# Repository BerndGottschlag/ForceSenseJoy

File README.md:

# ForceSenseJoy

This joystick measures the force applied by the user and not the deflection as done by conventional joysticks.

## Operating principle

The force is measured using two strain gauges each for the x- and y-axis.
These strain gauges are used in a half-bridge Wheatstone bridge configuration.
The signal from the bridge are amplified by an instrumentation amplifier and then read out using 13-bit analog-digital-converters.
The LUFA library is used to create a USB-joystick device.

## Status

At the moment there are some problems.
The calibration of the Wheatstone bridges is far from perfect.
On one hand this leads to a laborious adjustment process using the trim pots to balance the arms of the bridge and on the other hand the signal sometimes drifts over time.
While the adjustment does not have to be perfect, as the center point (zero) can be set via software on the press of a button,
a bigger imbalance of the bridges will make the amplifier to be unable to amplify the signal to its maximum amplitude.
A possible sollution to this would be the adjustment of the reference voltage.

## How to build
The make script is situated in firmware/src/.  
The project can be build and flashed with
```
make avrdude
```

## License

This project is licensed under the MIT License - see the [LICENSE](LICENSE) file for details

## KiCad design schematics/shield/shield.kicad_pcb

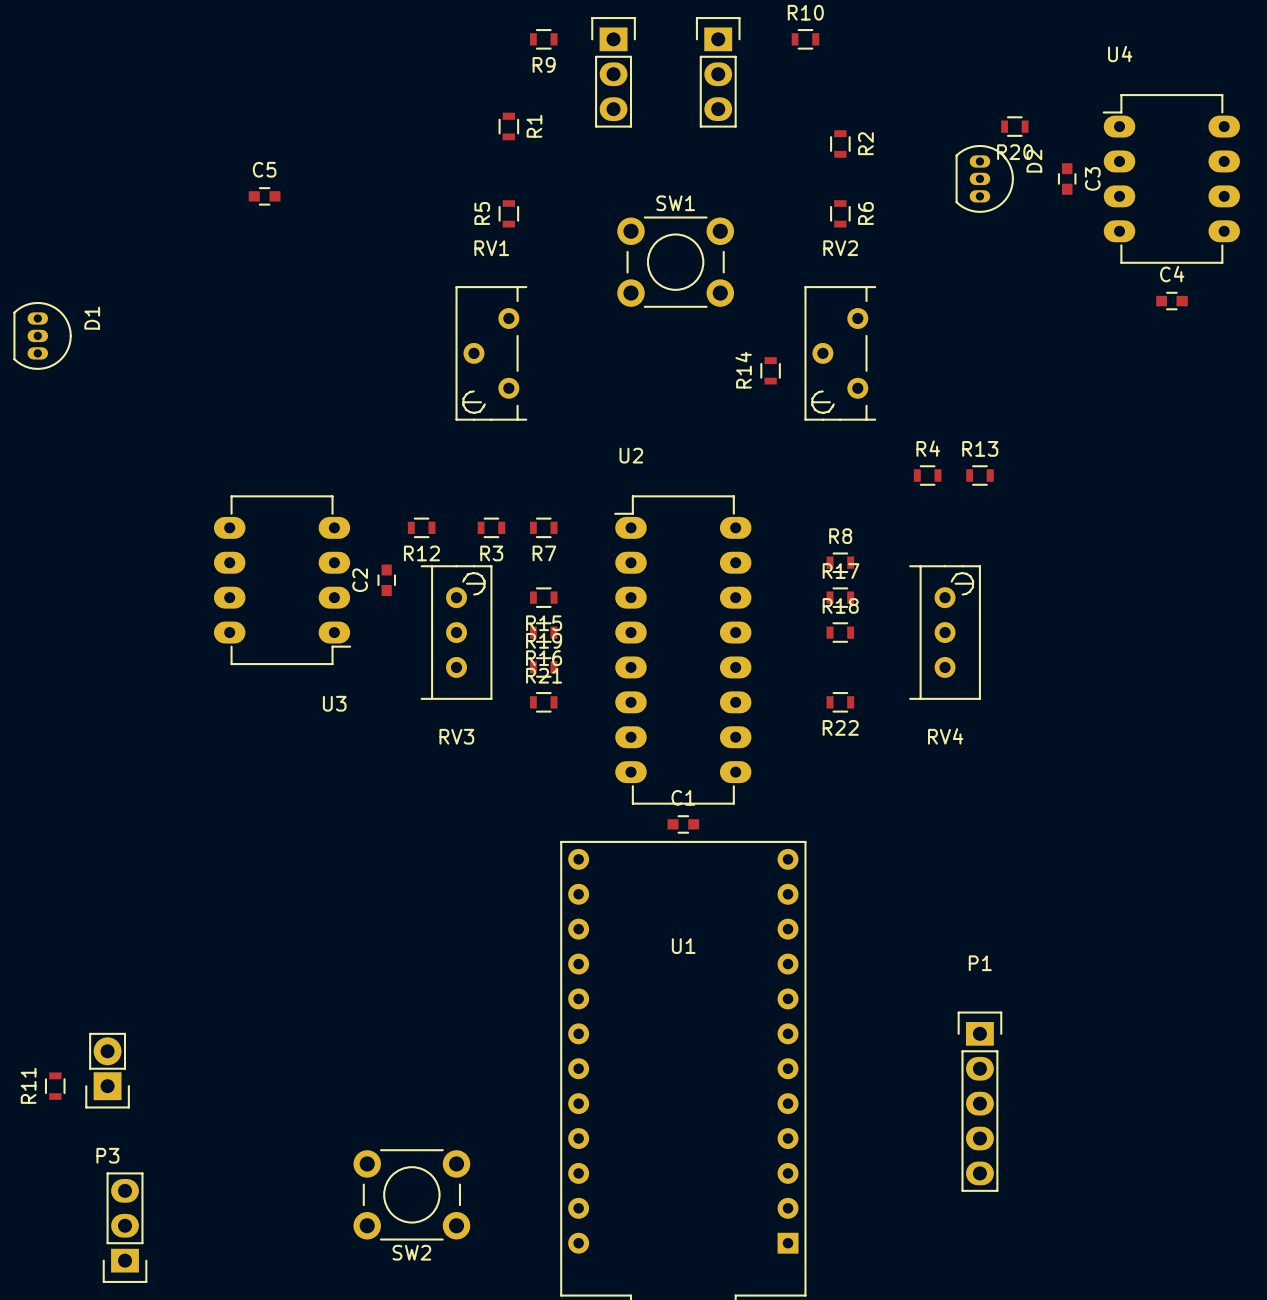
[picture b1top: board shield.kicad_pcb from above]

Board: 2 copper layers, 44 parts (0 on the bottom side), 45 nets, no tracks yet.

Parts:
C1, C4, C5: 1 uF; C_0603
C2, C3: 0.47uF; C_0603
D1, D2: LM385LP‑1‑2; TO-92_Inline_Narrow_Oval
P1: CONN_01X05; Pin_Header_Straight_1x05
P2, P4, P5: CONN_01X03; Pin_Header_Straight_1x03
P3: CONN_01X02; Pin_Header_Straight_1x02
R1, R2, R3, R4, R5, R6, R7, R8, R15, R17: 0; R_0603
R9, R10: 345; R_0603
R11: R; R_0603
R12, R13: 350; R_0603
R14: 10k; R_0603
R16, R18: 80; R_0603
R19, R20: 1K; R_0603
R21, R22: 1k; R_0603
RV1, RV2: 10; Potentiometer_Bourns_3296Y_3-8Zoll_Angular_ScrewUp
RV3, RV4: 100; Potentiometer_Bourns_3296W_3-8Zoll_Inline_ScrewUp
SW1, SW2: SW_PUSH; SW_PUSH_6mm
U1: ArduinoProMicro
U2: INA2126; DIP-16_W7.62mm_LongPads
U3, U4: MCP3301; DIP-8_W7.62mm_LongPads

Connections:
+5V: C1.2, C4.2, C5.2, P1.5, P2.3, P4.1, P5.1, R9.1, R10.1, SW1.1, U1.21, U2.9, U3.8, U4.8
Analog_out: P2.1, U1.17
CLK: U1.16, U3.7, U4.7
CLK_Shift: P1.2, U1.6
CS-A: U1.11, U3.5
CS-B: U1.12, U4.5
DATA_Shift: P1.1, U1.7
D_Out: U1.15, U3.6, U4.6
GND: C1.1, C4.1, C5.1, D1.2, D2.2, P1.4, P2.2, P4.3, P5.3, R11.1, R12.2, R13.2, R14.2, U1.3, U2.8, U3.4, U4.4
LATCH: P1.3, U1.5
LED: P3.2, U1.13
unnamed: C2.1, R21.1, U3.2
unnamed: C2.2, R19.1, U3.3
unnamed: C3.1, R22.1, U4.2
unnamed: C3.2, R20.1, U4.3
unnamed: P3.1, R11.2
unnamed: R1.1, R9.2
unnamed: R1.2, R5.2
unnamed: R2.2, R6.2
unnamed: R3.1, R7.2
unnamed: R4.1, R8.2
unnamed: R5.1, RV1.3
unnamed: R6.1, RV2.3
unnamed: R2.1, R10.2
unnamed: R3.2, R12.1
unnamed: R4.2, R13.1
unnamed: R14.1, SW1.2, U1.10
unnamed: R15.1, U2.3
unnamed: R15.2, RV3.1
unnamed: R16.1, U2.4
unnamed: R16.2, RV3.2
unnamed: R17.1, U2.14
unnamed: R17.2, RV4.1
unnamed: R18.1, U2.13
unnamed: R18.2, RV4.2
unnamed: SW2.1, U1.23
unnamed: SW2.2, U1.22
RefA: D1.1, R19.2, U2.5, U3.1
RefB: D2.1, R20.2, U4.1
V+inA: R7.1, RV1.2, U2.2
V+inB: R8.1, RV2.2, U2.15
V-inA: P4.2, U2.1
V-inB: P5.2, U2.16
VoutA: R21.2, U2.6, U2.7
VoutB: R22.2, U2.10, U2.11

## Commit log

2017-05-07 Initial commit without the LUFA-library
2017-05-07 Change symbol for the strain gauges
2017-05-07 Change configuration of the trim-pots for the bridge
    This change effects a easier calibration as it is less sensitive to
    changes.
    Furthermore it also seems to eliminate a certain creeping of the signal
    that was present before.
2017-05-14 Add LUFA as submodule
2017-05-21 Remove unused I2C-functions
2017-05-21 Add license (MIT)
2017-05-22 Add a license file
2018-02-10 Add .bin files to gitignore
2018-02-10 Update LUFA version
2018-02-10 Fix typo
2018-02-10 Clean up KiCad files
2018-02-10 Add first version of the readme
2018-02-10 Add a picture for the readme
